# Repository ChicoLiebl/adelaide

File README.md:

# Adelaide

Adelaide é um teclado 75% estilo Alice baseado no [Adelheid](https://github.com/floookay/adelheid) que é um fork do Arisu [Arisu PCB](https://github.com/FateNozomi/arisu-pcb)

Adelaide is a 75% Alice style keyboard based on [Adelheid](https://github.com/floookay/adelheid) which is a fork ofArisu [Arisu PCB](https://github.com/FateNozomi/arisu-pcb)

## ESSE PROJETO NÂO ESTÁ PRONTO NEM TESTADO
## THIS NOT FINISHED AND NOT TESTED

## Geração do case / Case generation

O script `scripts/gen-case-cad.sh` exporta as camadas do PCB como DXF e gera os modelos 3D do case (STEP) em `FAB-OUTPUTS/`. Se o PCB tiver as camadas `top.plate.split` (User.1) e `bottom.plate.split` (User.2) com linhas de corte, cada peça também é exportada dividida em duas metades (`-left`/`-right`) para caber em impressoras 3D menores — as linhas de corte diferentes do top e bottom fazem as emendas intertravarem na montagem. As peças inteiras continuam sendo exportadas para outros métodos de fabricação. Além dos moldes, os espaçadores em si também são exportados (`top-spacer`/`bottom-spacer`), úteis para imprimir e testar dimensões.

The `scripts/gen-case-cad.sh` script exports the PCB layers as DXF and generates the 3D case models (STEP) into `FAB-OUTPUTS/`. If the PCB has the `top.plate.split` (User.1) and `bottom.plate.split` (User.2) layers with cut lines, each part is also exported split into two halves (`-left`/`-right`) to fit smaller 3D printers — the different top and bottom cut lines make the seams interlock at assembly. The full parts are still exported for other fabrication methods. Besides the molds, the spacers themselves are also exported (`top-spacer`/`bottom-spacer`), useful for printing to test dimensions.

```sh
./scripts/gen-case-cad.sh pcb/adelaide.kicad_pcb
# ou / or
./scripts/gen-case-cad.sh macro-pad/macro-pad.kicad_pcb
```

### Dependências / Dependencies

- **git** — usado para nomear a pasta de saída / used to name the output folder
- **KiCad ≥ 9** (testado com/tested with 10.0.5) — o comando `kicad-cli` precisa estar no PATH / the `kicad-cli` command must be on PATH
- **FreeCAD ≥ 1.0** (testado com/tested with 1.1.3) — o comando `freecadcmd` precisa estar no PATH / the `freecadcmd` command must be on PATH

Os scripts Python (`dxf_to_solid.py`, `generate_mold.py`) rodam dentro do Python embutido do FreeCAD, então não é necessário instalar pacotes com pip. O importador DXF legado (`importDXF`) já vem incluído no Draft workbench do FreeCAD 1.x.

The Python scripts (`dxf_to_solid.py`, `generate_mold.py`) run inside FreeCAD's bundled Python, so no pip packages are needed. The legacy DXF importer (`importDXF`) ships with FreeCAD 1.x's Draft workbench.

**Nota / Note:** instalações via Flatpak/Snap não expõem `freecadcmd` diretamente no PATH — prefira o pacote nativo da sua distro ou o AppImage. / Flatpak/Snap installs don't expose `freecadcmd` directly on PATH — prefer your distro's native package or the AppImage.

## Firmware (QMK)

O script `scripts/build-qmk.sh` compila o firmware dos dois teclados (`qmk/adelaide` e `qmk/my_numpad`) e copia os binários `.hex` para `FAB-OUTPUTS/firmware-<data>-<versão>/`. Na primeira execução ele clona o `qmk_firmware` (shallow) em `~/qmk_firmware` (configurável via variável `QMK_HOME`) e cria symlinks dos teclados deste repositório dentro dele.

The `scripts/build-qmk.sh` script builds the firmware for both keyboards (`qmk/adelaide` and `qmk/my_numpad`) and copies the `.hex` binaries to `FAB-OUTPUTS/firmware-<date>-<version>/`. On first run it shallow-clones `qmk_firmware` into `~/qmk_firmware` (configurable via the `QMK_HOME` env var) and symlinks this repo's keyboards into it.

```sh
./scripts/build-qmk.sh
```

### Dependências / Dependencies

- **qmk CLI** (testado com/tested with 1.2.0)
- **avr-gcc** + avr-libc
- **git**

## TO-DO

    - Case project

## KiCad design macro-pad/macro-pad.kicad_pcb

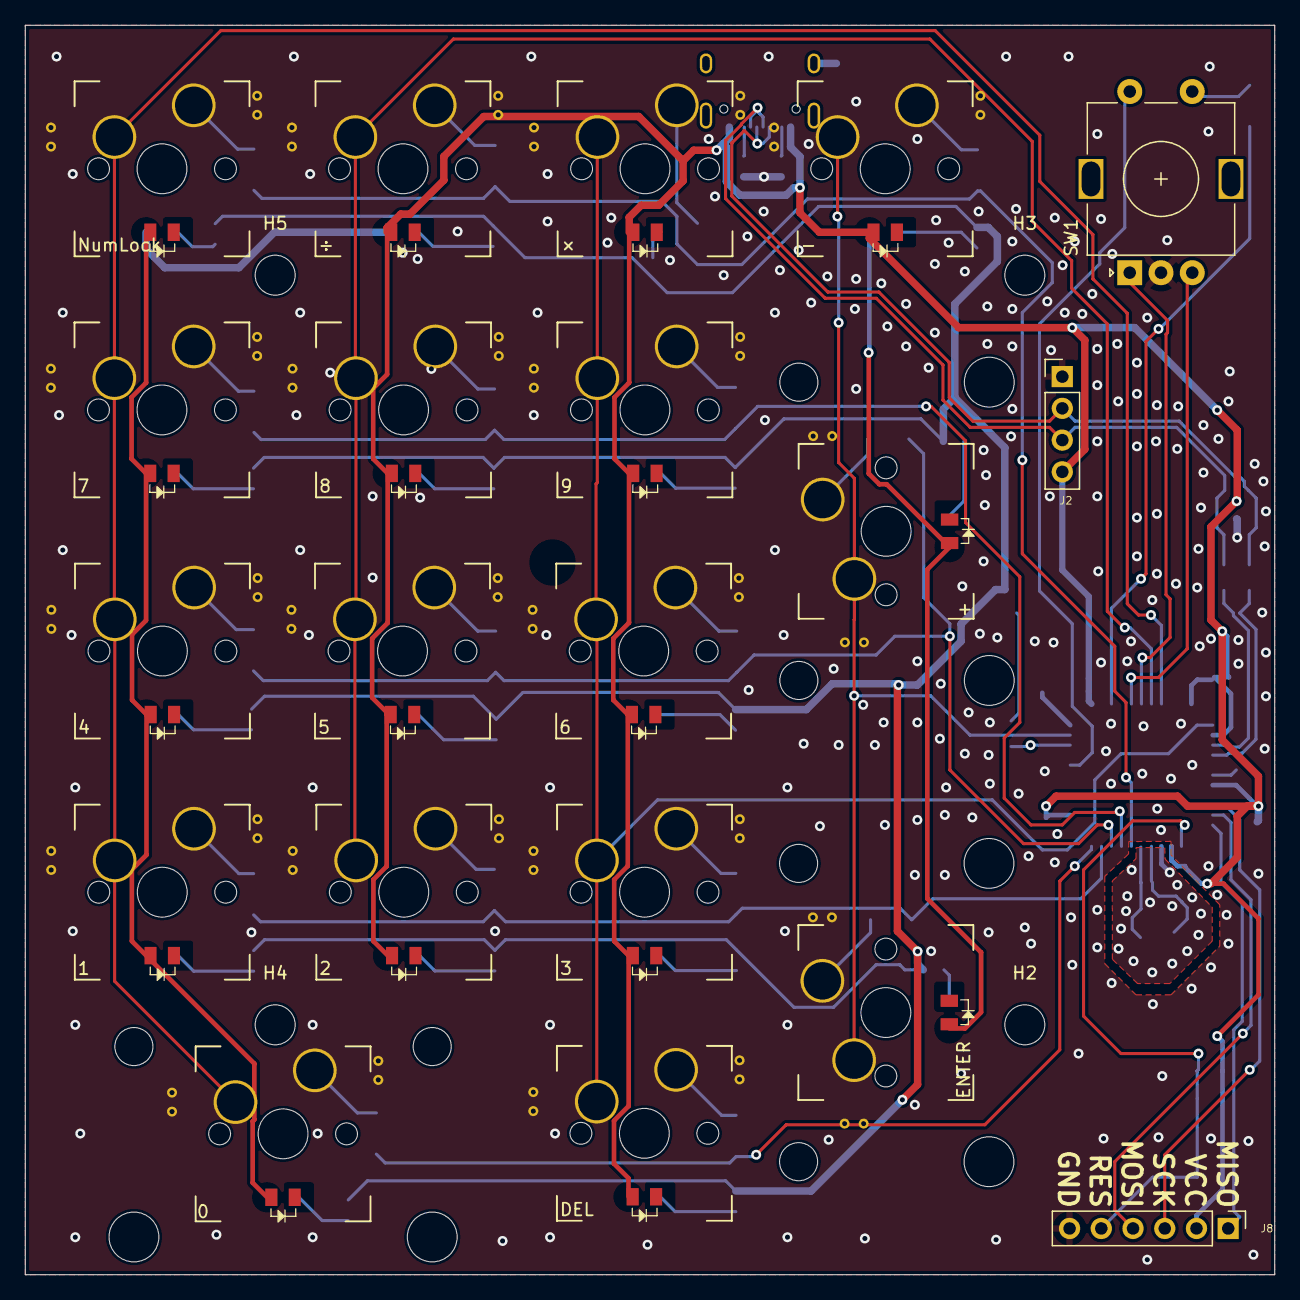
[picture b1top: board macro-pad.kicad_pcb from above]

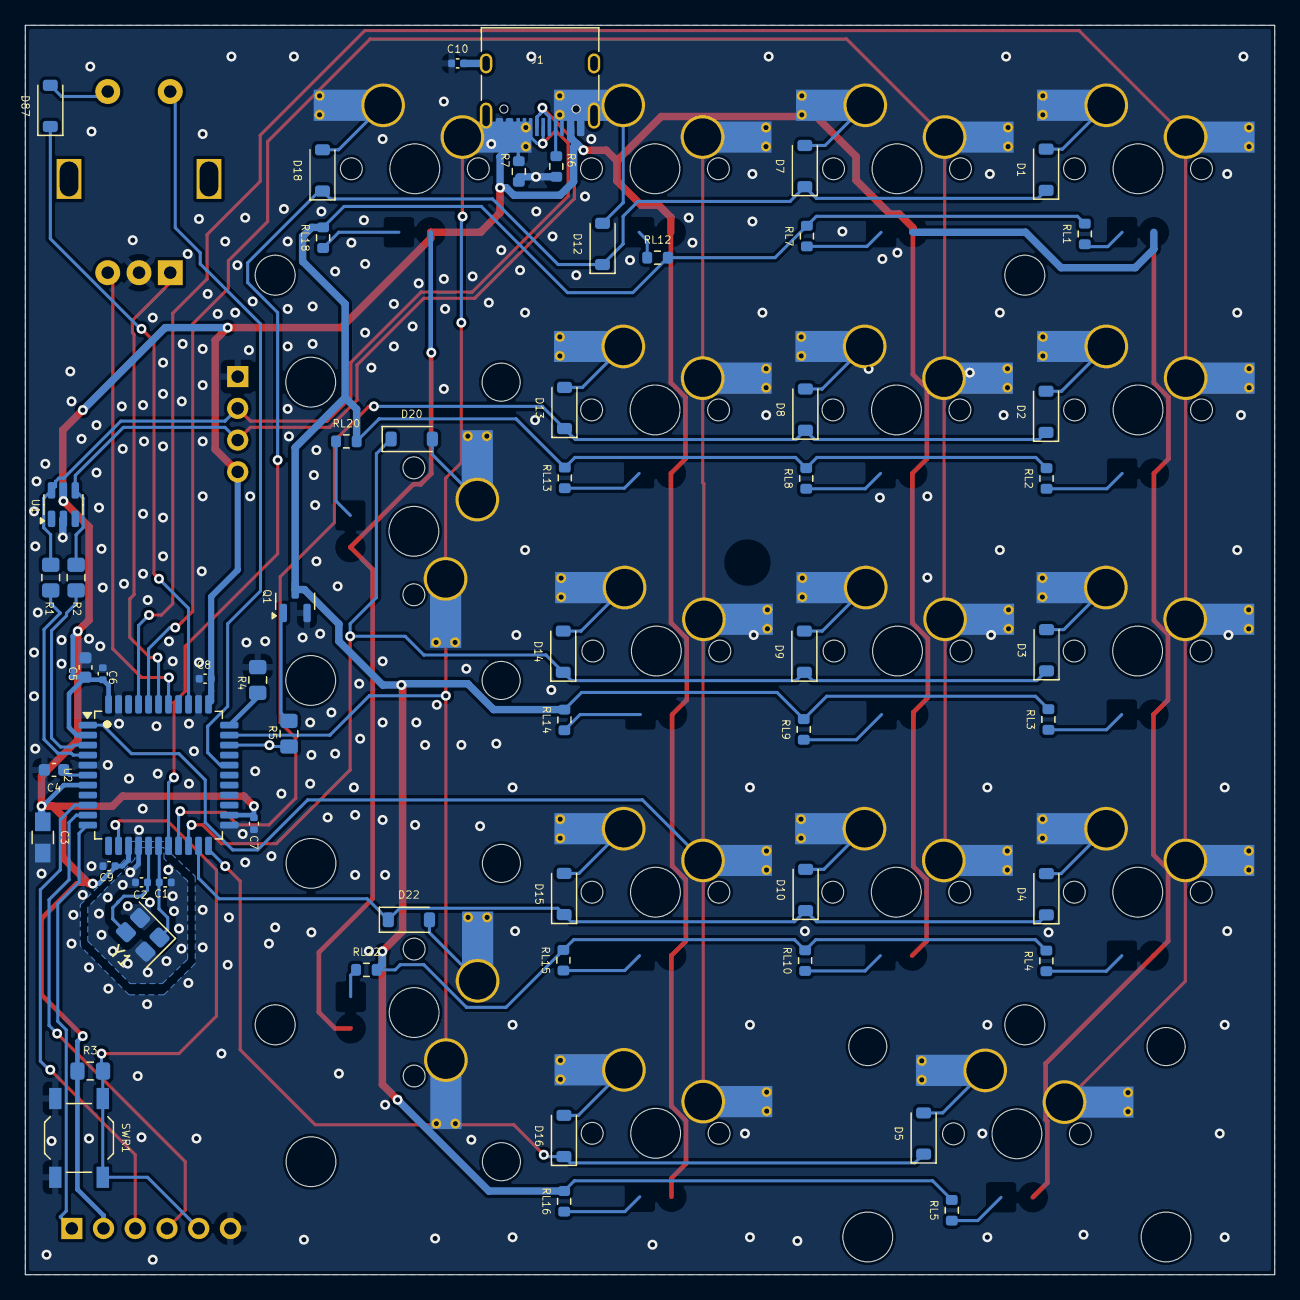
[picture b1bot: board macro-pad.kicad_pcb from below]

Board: 2 copper layers, 100.0 x 100.0 mm, 82 parts (58 on the bottom side), 68 nets.

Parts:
C1, C2: 22pF; C_0402_1005Metric
C3: 10uF; C_0805_HandSoldering
C4: 1uF (±10%); C_0603_1608Metric
C5: 1uF; C_0603_1608Metric
C6, C7, C8, C9, C10: 0.1uF; C_0402_1005Metric
D1, D2, D3, D4, D5, D7, D8, D9, D10, D12, D13, D14, D15, D16, D18, D20, D22, D87: D; D_SOD-123
H2, H3, H4, H5: MountingHole; MountingHole_3.2mm_M3
J1: USB_C_Receptacle_USB2.0; USB_C_Receptacle_HRO_TYPE-C-31-M-12
J2: Conn_01x04; PinHeader_1x04_P2.54mm_Vertical
J8: Conn_01x06; PinHeader_1x06_P2.54mm_Vertical
MX1: NumLock; MXOnly-1U-Hotswap-Antishear-Led-SMD
MX2: 7; MXOnly-1U-Hotswap-Antishear-Led-SMD
MX3: 4; MXOnly-1U-Hotswap-Antishear-Led-SMD
MX4: 1; MXOnly-1U-Hotswap-Antishear-Led-SMD
MX5: 0; MXOnly-2U-Hotswap-Antishear-Led-SMD
MX7: ÷; MXOnly-1U-Hotswap-Antishear-Led-SMD
MX8: 8; MXOnly-1U-Hotswap-Antishear-Led-SMD
MX9: 5; MXOnly-1U-Hotswap-Antishear-Led-SMD
MX10: 2; MXOnly-1U-Hotswap-Antishear-Led-SMD
MX12: ×; MXOnly-1U-Hotswap-Antishear-Led-SMD
MX13: 9; MXOnly-1U-Hotswap-Antishear-Led-SMD
MX14: 6; MXOnly-1U-Hotswap-Antishear-Led-SMD
MX15: 3; MXOnly-1U-Hotswap-Antishear-Led-SMD
MX16: DEL; MXOnly-1U-Hotswap-Antishear-Led-SMD
MX18: -; MXOnly-1U-Hotswap-Antishear-Led-SMD
MX20: +; MXOnly-2U-Hotswap-Antishear-Led-SMD
MX22: ENTER; MXOnly-2U-Hotswap-Antishear-Led-SMD
Q1: 2N7002; SOT-23
R1, R2: 22; R_0805_2012Metric_Pad1.15x1.40mm_HandSolder
R3, R4: 10K; R_0805_2012Metric_Pad1.15x1.40mm_HandSolder
R5: 1.5K; R_0805_2012Metric_Pad1.15x1.40mm_HandSolder
R6, R7: 5K1; R_0603_1608Metric
RL1, RL2, RL3, RL4, RL5, RL7, RL8, RL9, RL10, RL12, RL13, RL14, RL15, RL16, RL18, RL20, RL22: R; R_0603_1608Metric
SW1: Rotary_Encoder_Switch; RotaryEncoder_Alps_EC11E-Switch_Vertical_H20mm
SWR1: SW_Push; SW_SPST_TL3342
U1: USBLC6-2SC6; SOT-23-6
U2: ATmega32U4-AU; TQFP-44_10x10mm_P0.8mm
Y1: Crystal_GND24; Crystal_SMD_SeikoEpson_FA238-4Pin_3.2x2.5mm

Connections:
/COND+: J1.A6 (D+), J1.B6 (D+), J2.2, R1.2, U1.6 (IO1)
/COND-: J1.A7 (D-), J1.B7 (D-), J2.3, R2.2, U1.4 (IO2)
/MISO: J8.1, U2.11 (PB3)
/MOSI: J8.4, U2.10 (PB2)
/SCK: J8.3, U2.9 (PB1)
/col0: MX1.1 (COL), MX2.1 (COL), MX3.1 (COL), MX4.1 (COL), MX5.1 (COL), U2.41 (PF0)
/col1: MX7.1 (COL), MX8.1 (COL), MX9.1 (COL), MX10.1 (COL), U2.40 (PF1)
/col2: MX12.1 (COL), MX13.1 (COL), MX14.1 (COL), MX15.1 (COL), MX16.1 (COL), U2.1 (PE6)
/col3: MX18.1 (COL), MX20.1 (COL), MX22.1 (COL), U2.32 (PC7)
/col10: SW1.S2, U2.29 (PB5)
/enc1: SW1.A, U2.39 (PF4)
/enc2: SW1.B, U2.38 (PF5)
/ledGND: Q1.3 (D), RL1.2, RL2.2, RL3.2, RL4.2, RL5.2, RL7.2, RL8.2, RL9.2, RL10.2, RL12.2, RL13.2, RL14.2, RL15.2, RL16.2, RL18.2, RL20.2, RL22.2
/row0: D1.1 (K), D7.1 (K), D12.1 (K), D18.1 (K), U2.18 (PD0)
/row1: D2.1 (K), D8.1 (K), D13.1 (K), U2.19 (PD1)
/row2: D3.1 (K), D9.1 (K), D14.1 (K), D20.1 (K), U2.20 (PD2)
/row3: D4.1 (K), D10.1 (K), D15.1 (K), D22.1 (K), U2.21 (PD3)
/row4: D5.1 (K), D16.1 (K), U2.22 (PD5)
/row5: D87.1 (K), U2.36 (PF7)
/~RES: J8.5, R3.2, SWR1.2, U2.13 (~RESET)
D+: R1.1, U2.4 (D+)
D-: R2.1, U2.3 (D-)
GND: C1.1, C2.2, C3.2, C4.2, C5.2, C6.2, C7.2, C8.2, C9.2, C10.1, J1.A1 (GND), J1.A12 (GND), J1.B1 (GND), J1.B12 (GND), J2.1, J8.6, Q1.2 (S), R4.2, R6.1, R7.2, SW1.C, SWR1.1, U1.2 (GND), U2.5 (UGND), U2.15 (GND), U2.23 (GND), U2.35 (GND), U2.43 (GND), Y1.2, Y1.4
unnamed: D1.2 (A), MX1.2 (ROW)
unnamed: D2.2 (A), MX2.2 (ROW)
unnamed: D3.2 (A), MX3.2 (ROW)
unnamed: D4.2 (A), MX4.2 (ROW)
unnamed: D5.2 (A), MX5.2 (ROW)
unnamed: D7.2 (A), MX7.2 (ROW)
unnamed: D8.2 (A), MX8.2 (ROW)
unnamed: D9.2 (A), MX9.2 (ROW)
unnamed: D10.2 (A), MX10.2 (ROW)
unnamed: D12.2 (A), MX12.2 (ROW)
unnamed: D13.2 (A), MX13.2 (ROW)
unnamed: D14.2 (A), MX14.2 (ROW)
unnamed: D15.2 (A), MX15.2 (ROW)
unnamed: D16.2 (A), MX16.2 (ROW)
unnamed: D18.2 (A), MX18.2 (ROW)
unnamed: D20.2 (A), MX20.2 (ROW)
unnamed: D22.2 (A), MX22.2 (ROW)
unnamed: D87.2 (A), SW1.S1
unnamed: J1.A5 (CC1), R6.2
unnamed: J1.B5 (CC2), R7.1
unnamed: C10.2, J1.S1 (SHIELD)
unnamed: MX1.4 (LEDGND), RL1.1
unnamed: MX2.4 (LEDGND), RL2.1
unnamed: MX3.4 (LEDGND), RL3.1
unnamed: MX4.4 (LEDGND), RL4.1
unnamed: MX5.4 (LEDGND), RL5.1
unnamed: MX7.4 (LEDGND), RL7.1
unnamed: MX8.4 (LEDGND), RL8.1
unnamed: MX9.4 (LEDGND), RL9.1
unnamed: MX10.4 (LEDGND), RL10.1
unnamed: MX12.4 (LEDGND), RL12.1
unnamed: MX13.4 (LEDGND), RL13.1
unnamed: MX14.4 (LEDGND), RL14.1
unnamed: MX15.4 (LEDGND), RL15.1
unnamed: MX16.4 (LEDGND), RL16.1
unnamed: MX18.4 (LEDGND), RL18.1
unnamed: MX20.4 (LEDGND), RL20.1
unnamed: MX22.4 (LEDGND), RL22.1
unnamed: Q1.1 (G), R5.2
unnamed: R5.1, U2.31 (PC6)
unnamed: C4.1, U2.6 (UCAP)
unnamed: R4.1, U2.33 (~HWB/PE2)
VCC: C3.1, C5.1, C6.1, C7.1, C8.1, C9.1, J1.A4 (VBUS), J1.A9 (VBUS), J1.B4 (VBUS), J1.B9 (VBUS), J2.4, J8.2, MX1.3 (LED), MX2.3 (LED), MX3.3 (LED), MX4.3 (LED), MX5.3 (LED), MX7.3 (LED), MX8.3 (LED), MX9.3 (LED), MX10.3 (LED), MX12.3 (LED), MX13.3 (LED), MX14.3 (LED), MX15.3 (LED), MX16.3 (LED), MX18.3 (LED), MX20.3 (LED), MX22.3 (LED), R3.1, U1.5 (VBUS), U2.2 (UVCC), U2.7 (VBUS), U2.14 (VCC), U2.24 (AVCC), U2.34 (VCC), U2.44 (AVCC)
XTAL1: C1.2, U2.17 (XTAL1), Y1.1
XTAL2: C2.1, U2.16 (XTAL2), Y1.3

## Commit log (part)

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2024-10-01 cleanup project
2024-10-01 added readme
2024-11-04 changes key footprints to hotswap + SMD LEDs
2024-11-04 renamed files
2024-11-09 improved ground plane continuity
2024-12-10 improved power connections
2024-12-11 added fabrication output script
2024-12-11 updated USB tracks to 90 ohm
2024-12-23 made tracks round
2024-12-23 add macro pad
2025-09-05 add numpad qmk config
2025-09-06 add case plates generation
2025-09-08 add freecadcmd svg to solid script
2025-09-10 added svg_to_solid.py
2025-09-10 update lib for correct cad generation
2025-09-11 updated case scripts to use dxf files
2025-09-11 added mounting holes + fix edge cuts
2025-09-12 updated script to handle holes in other way
2025-09-12 add top plate cut for stabilizer
2025-09-12 optimized python scripts
2025-09-12 fix scripts
2025-09-12 fixed stabilizer cutout
2025-09-13 fixed qmk configuration
2025-09-15 fixed bottom courtyard
2026-04-26 fix files on new kicad version
